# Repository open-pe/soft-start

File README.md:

Simple soft start circuit with power MOSFET and NTC.
It is designed to limit in-rush current of a DCDC converter connected to a battery with XT90i (like XT90 + 2 signal pins) connectors. 
The additional signal pin makes sure that the circuit resets after the connector is unplugged. Otherwise, it can be powered by the input capacitor of the load and doesn't "know" that the battery power is lost.
Because battery voltage changes with battery SoC, absolute voltage at load input cannot tell wether the input capacitance is fully charged.

The 78L15 is the power supply for MOSFET driving and is a reference voltage at the same time. Q2 protects the NTC from long current exposure if the connector is plugged in to slowly or not properly.
The comparator switches on once the voltage drop accross the NTC falls below the value defined by the potentiometer and R1,R2. With the given resistor values, the circuit works with battery voltage upto 60V.
Note that 78L15 max input is 30V.

You can omit and short Q2 if you dont use a seperate power supply for circuit.

NTCs
https://datasheetspdf.com/pdf/814993/EXSENSE/NTC-10D7/1

MOSFETS

* IPP024N08NF2SAKMA1 (80V, 2.4mohm, Id100 139A)
* IRF100B201 (100V, 4.2mohm, Id100 136A)

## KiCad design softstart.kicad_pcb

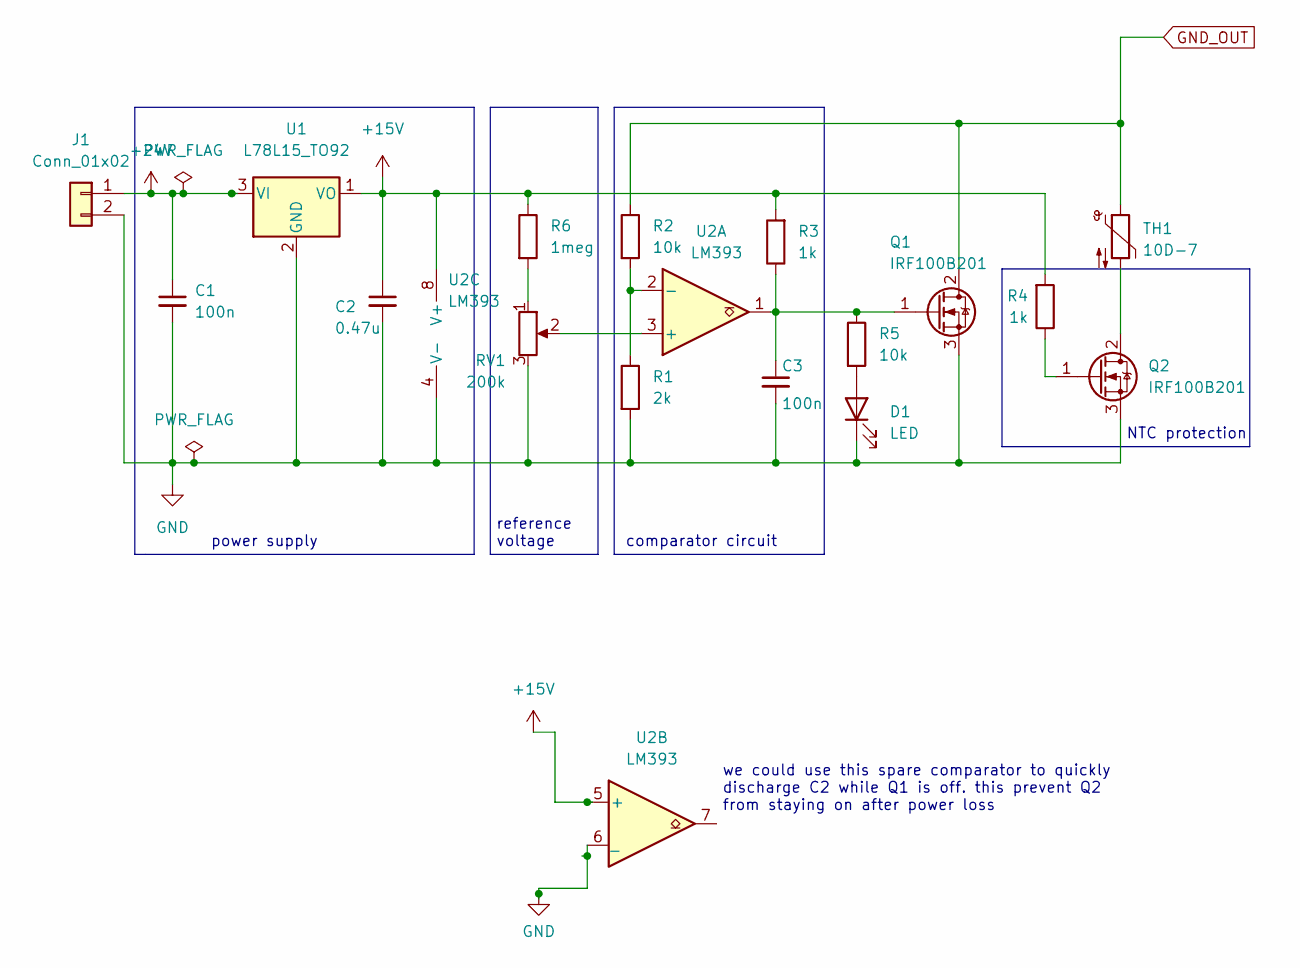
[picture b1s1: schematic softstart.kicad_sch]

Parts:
C1, C3: 100n; C_0603_1608Metric_Pad1.08x0.95mm_HandSolder
C2: 0.47u; C_0805_2012Metric_Pad1.18x1.45mm_HandSolder
D1: LED; LED_D5.0mm
J1: Conn_01x02; PinHeader_1x02_P2.54mm_Vertical
Q1: IRF100B201; TO-220-3_Horizontal_TabDown
Q2: IRF100B201; TO-220-3_Vertical
R1: 2k; R_0805_2012Metric_Pad1.20x1.40mm_HandSolder
R2, R5: 10k; R_0805_2012Metric_Pad1.20x1.40mm_HandSolder
R3, R4: 1k; R_0805_2012Metric_Pad1.20x1.40mm_HandSolder
R6: 1meg; R_0805_2012Metric_Pad1.20x1.40mm_HandSolder
RV1: 200k; Potentiometer_Bourns_3296W_Vertical
TH1: 10D-7; R_Axial_DIN0207_L6.3mm_D2.5mm_P7.62mm_Horizontal
U1: L78L15_TO92; TO-92_Inline
U2: LM393; DIP-8_W7.62mm

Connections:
+15V: C2.1, R3.2, R4.2, R6.1, U1.1 (VO), U2.5 (+), U2.8 (V+)
+24V: C1.1, J1.1, U1.3 (VI)
GND: C1.2, C2.2, C3.2, D1.1 (K), J1.2, Q1.3 (S), Q2.3 (S), R1.2, RV1.3, U1.2 (GND), U2.4 (V-), U2.6 (_)
GND_OUT: Q1.2 (D), R2.1, TH1.1
unnamed: D1.2 (A), R5.2
unnamed: C3.1, Q1.1 (G), R3.1, R5.1, U2.1
unnamed: Q2.1 (G), R4.1
unnamed: Q2.2 (D), TH1.2
unnamed: R1.1, R2.2, U2.2 (-)
unnamed: R6.2, RV1.1
unnamed: RV1.2, U2.3 (+)

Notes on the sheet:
NTC protection
we could use this spare comparator to quickly discharge C2 while Q1 is off. this prevent Q2 from staying on after power loss
power supply
reference voltage
comparator circuit

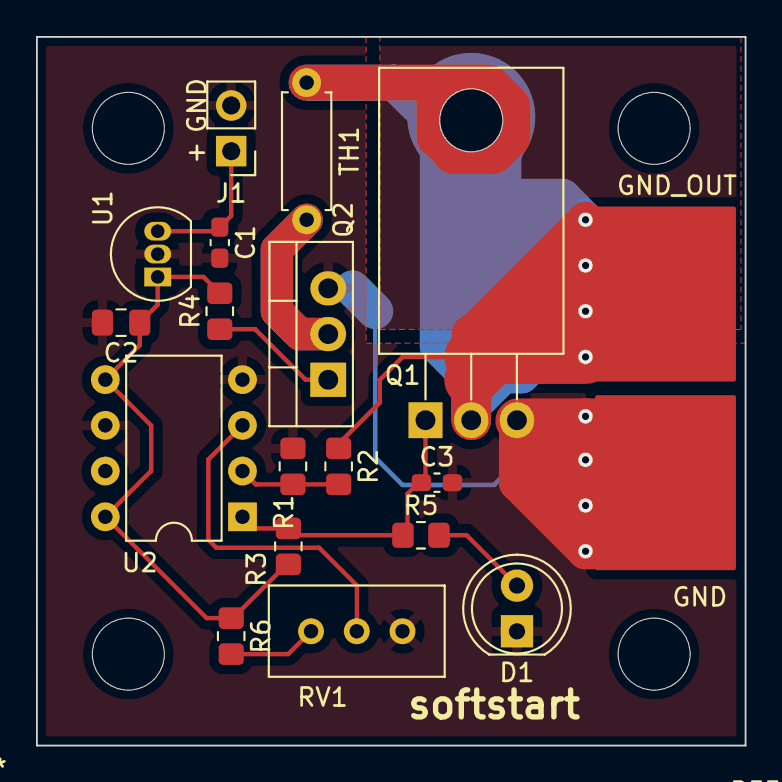
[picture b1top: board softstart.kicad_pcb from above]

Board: 2 copper layers, 39.4 x 39.4 mm, 17 parts (0 on the bottom side), 11 nets.

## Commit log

2022-10-02 add kicad project
2023-03-27 fix comp output
